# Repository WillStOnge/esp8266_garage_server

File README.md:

# ESP8266 Garage Server

This is intended for use with a Homebridge server which interacts with this 'API'. My implementation can be found at [WillStOnge/homebridge-garagedoor-esp8266](https://github.com/WillStOnge/homebridge-garagedoor-esp8266)

## Configuration
There isn't too much to configure. All you need to do is enter your network SSID and password into the define statements on lines 14 and 15. If you want the relay to remain on for more/less time, this can be altered on line 11 (time is in milliseconds). Also, make sure that your relay and sensors are on the same GPIO lines as described on lines 7, 8, and 9.

## Wiring Diagram
I used an ESP8266 develoment board and some blank PCBs for ease of soldering.

This is the schematic for this setup:

It doesn't include the ESP8266, but the GPIO lines are clearly labeled. When attaching to your garage, make sure your lines are not backwards or the door will not open/close.

This is the final PCB:

I decided to solder it to a blank PCB since soldering open is sketchy and messy. I then threw it in a plastic box and sealed it off to prevent bugs/dust from getting in.

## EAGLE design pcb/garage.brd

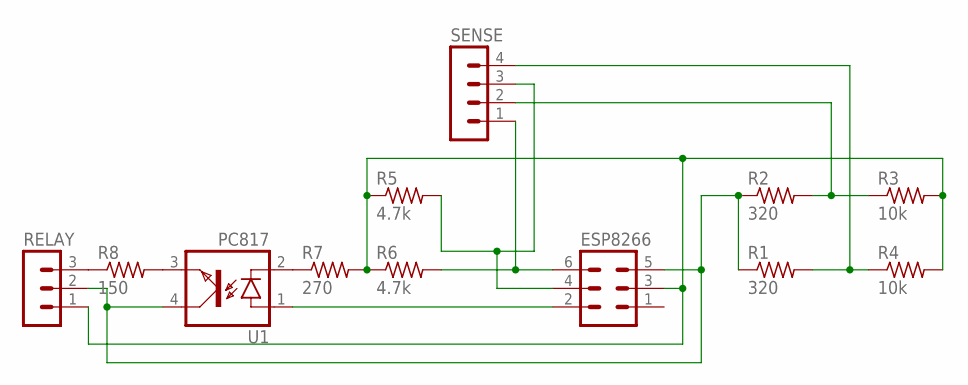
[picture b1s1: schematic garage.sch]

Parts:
ESP8266: MA03-2
R1, R2: 320; 0207/2V
R3, R4: 10k; 0207/2V
R5, R6: 4.7k; 0207/2V
R7: 270; 0207/2V
R8: 150; 0207/2V
RELAY: MA03-1
SENSE: MA04-1
U1: PC817; DIL04

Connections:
unnamed: ESP8266.2, U1.1 (A)
unnamed: ESP8266.6, R6.2, SENSE.1
unnamed: R8.1, RELAY.3
unnamed: R2.2, R3.1, SENSE.2
unnamed: R1.2, R4.1, SENSE.4
unnamed: ESP8266.3, R3.2, R4.2, R5.1, R6.1, R7.2, RELAY.1
unnamed: ESP8266.5, R1.1, R2.1, RELAY.2, U1.4 (COL)
unnamed: R7.1, U1.2 (C)
unnamed: ESP8266.4, R5.2, SENSE.3
unnamed: R8.2, U1.3 (EMIT)

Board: 2 copper layers, 12 parts (0 on the bottom side), 10 nets, no tracks yet.

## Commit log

2020-12-07 Added schematic to README
2020-12-07 Forgot the !
2020-12-07 Added Arduino code
2020-12-07 Updated README with new images
2020-12-21 Added eagle files
